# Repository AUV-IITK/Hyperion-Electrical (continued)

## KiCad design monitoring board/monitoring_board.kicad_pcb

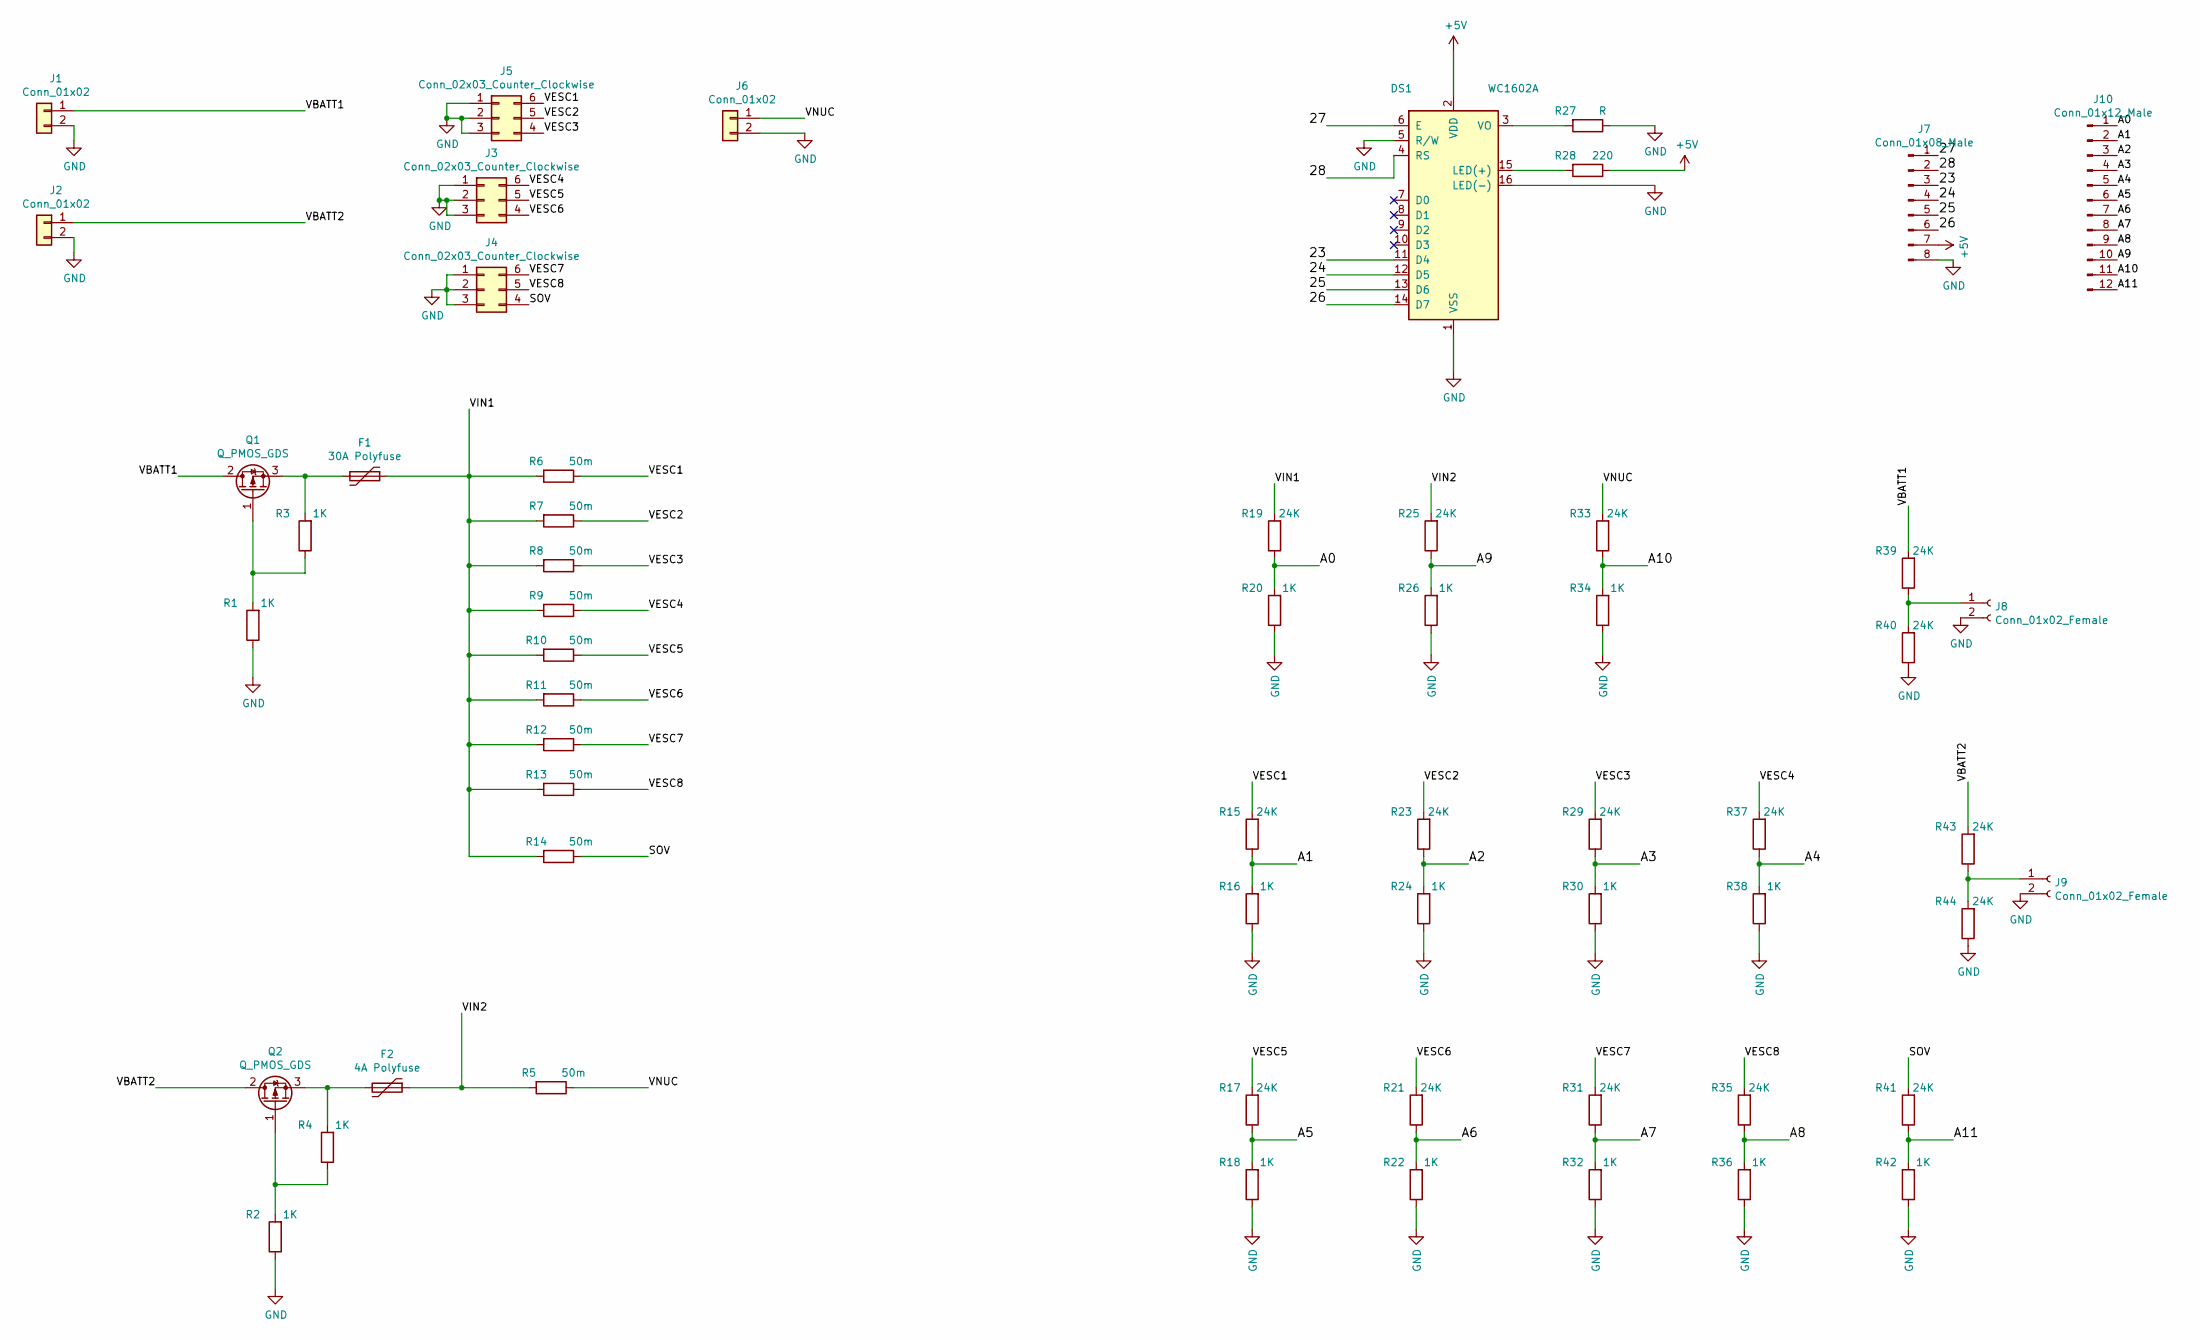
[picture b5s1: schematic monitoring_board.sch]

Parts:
DS1: WC1602A
F1: 30A Polyfuse; Fuse_TE5_Littlefuse-395Series
F2: 4A Polyfuse; Fuse_TE5_Littlefuse-395Series
J1, J2, J6: Conn_01x02; TerminalBlock_bornier-2_P5.08mm
J3, J4, J5: Conn_02x03_Counter_Clockwise; Molex_mlx32_straight_header_6.35mm
J7: Conn_01x08_Male; PinHeader_1x08_P2.54mm_Vertical
J8, J9: Conn_01x02_Female; PinSocket_1x02_P2.54mm_Vertical
J10: Conn_01x12_Male; PinHeader_1x12_P2.54mm_Vertical
Q1, Q2: Q_PMOS_GDS; TO-252-2
R1, R2, R3, R4, R16, R18, R20, R22, R24, R26, R30, R32, R34, R36, R38, R42: 1K; R_1206_3216Metric_Pad1.42x1.75mm_HandSolder
R5, R6, R7, R8, R9, R10, R11, R12, R13, R14: 50m; R_1206_3216Metric_Pad1.42x1.75mm_HandSolder
R15, R17, R19, R21, R23, R25, R29, R31, R33, R35, R37, R39, R40, R41, R43, R44: 24K; R_1206_3216Metric_Pad1.42x1.75mm_HandSolder
R27: R; R_1206_3216Metric_Pad1.42x1.75mm_HandSolder
R28: 220; R_1206_3216Metric_Pad1.42x1.75mm_HandSolder

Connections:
+5V: DS1.2 (VDD), J7.7, R28.1
/23: DS1.11 (D4), J7.3
/24: DS1.12 (D5), J7.4
/25: DS1.13 (D6), J7.5
/26: DS1.14 (D7), J7.6
/27: DS1.6 (E), J7.1
/28: DS1.4 (RS), J7.2
/A0: J10.1, R19.1, R20.2
/A1: J10.2, R15.1, R16.2
/A2: J10.3, R23.1, R24.2
/A3: J10.4, R29.1, R30.2
/A4: J10.5, R37.1, R38.2
/A5: J10.6, R17.1, R18.2
/A6: J10.7, R21.1, R22.2
/A7: J10.8, R31.1, R32.2
/A8: J10.9, R35.1, R36.2
/A9: J10.10, R25.1, R26.2
/A10: J10.11, R33.1, R34.2
/A11: J10.12, R41.1, R42.2
/SOV: J4.4, R14.1, R41.2
/VBATT1: J1.1, Q1.2 (D), R39.2
/VBATT2: J2.1, Q2.2 (D), R43.2
/VESC1: J5.6, R6.1, R15.2
/VESC2: J5.5, R7.1, R23.2
/VESC3: J5.4, R8.1, R29.2
/VESC4: J3.6, R9.1, R37.2
/VESC5: J3.5, R10.1, R17.2
/VESC6: J3.4, R11.1, R21.2
/VESC7: J4.6, R12.1, R31.2
/VESC8: J4.5, R13.1, R35.2
/VIN1: F1.1, R6.2, R7.2, R8.2, R9.2, R10.2, R11.2, R12.2, R13.2, R14.2, R19.2
/VIN2: F2.1, R5.2, R25.2
/VNUC: J6.1, R5.1, R33.2
GND: DS1.1 (VSS), DS1.5 (R/W), DS1.16 (LED(-)), J1.2, J2.2, J3.1, J3.2, J3.3, J4.1, J4.2, J4.3, J5.1, J5.2, J5.3, J6.2, J7.8, J8.2, J9.2, R1.1, R2.1, R16.1, R18.1, R20.1, R22.1, R24.1, R26.1, R27.1, R30.1, R32.1, R34.1, R36.1, R38.1, R40.1, R42.1, R44.1
unnamed: DS1.3 (VO), R27.2
unnamed: DS1.15 (LED(+)), R28.2
unnamed: F1.2, Q1.3 (S), R3.2
unnamed: F2.2, Q2.3 (S), R4.2
unnamed: J8.1, R39.1, R40.2
unnamed: J9.1, R43.1, R44.2
unnamed: Q1.1 (G), R1.2, R3.1
unnamed: Q2.1 (G), R2.2, R4.1

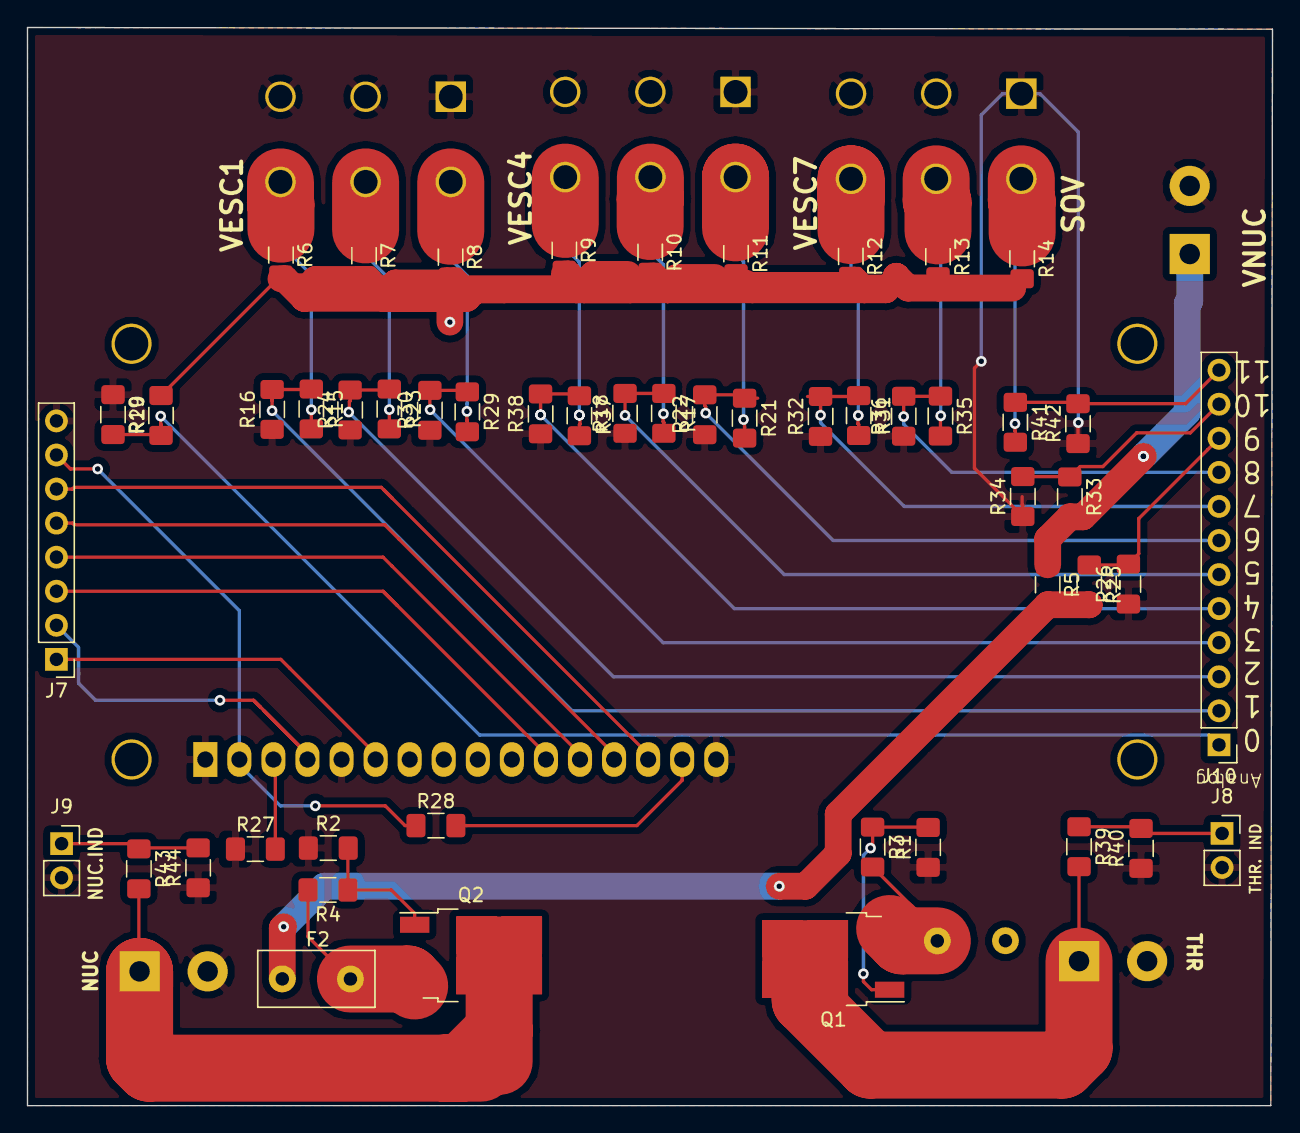
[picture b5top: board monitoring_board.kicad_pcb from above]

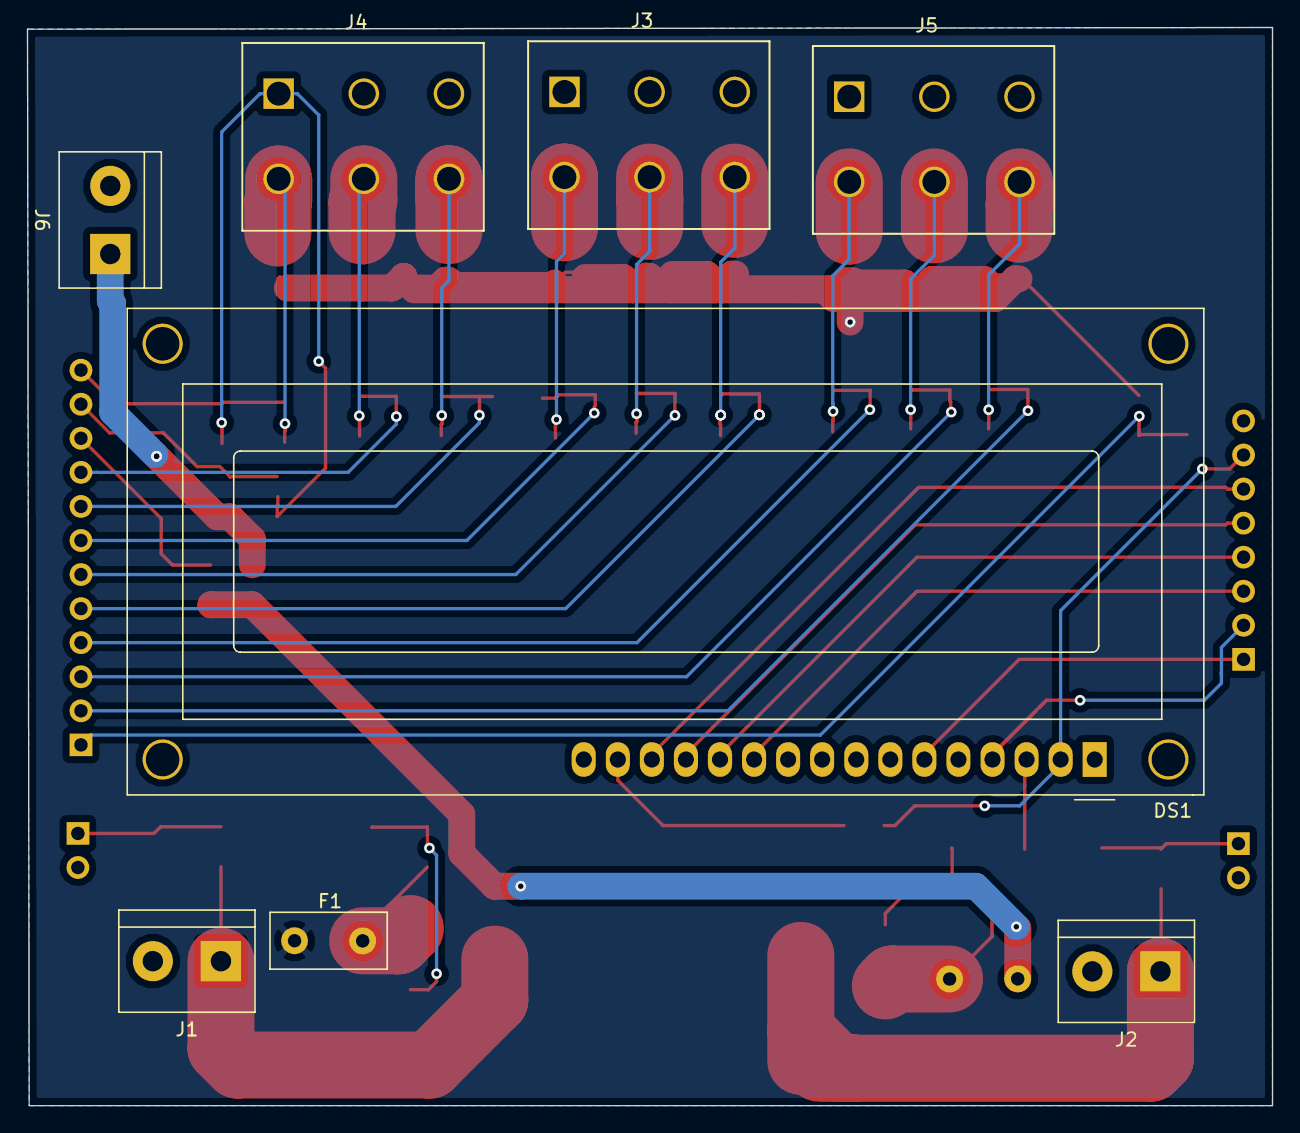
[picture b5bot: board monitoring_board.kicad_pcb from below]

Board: 2 copper layers, 92.8 x 80.4 mm, 59 parts (8 on the bottom side), 42 nets.

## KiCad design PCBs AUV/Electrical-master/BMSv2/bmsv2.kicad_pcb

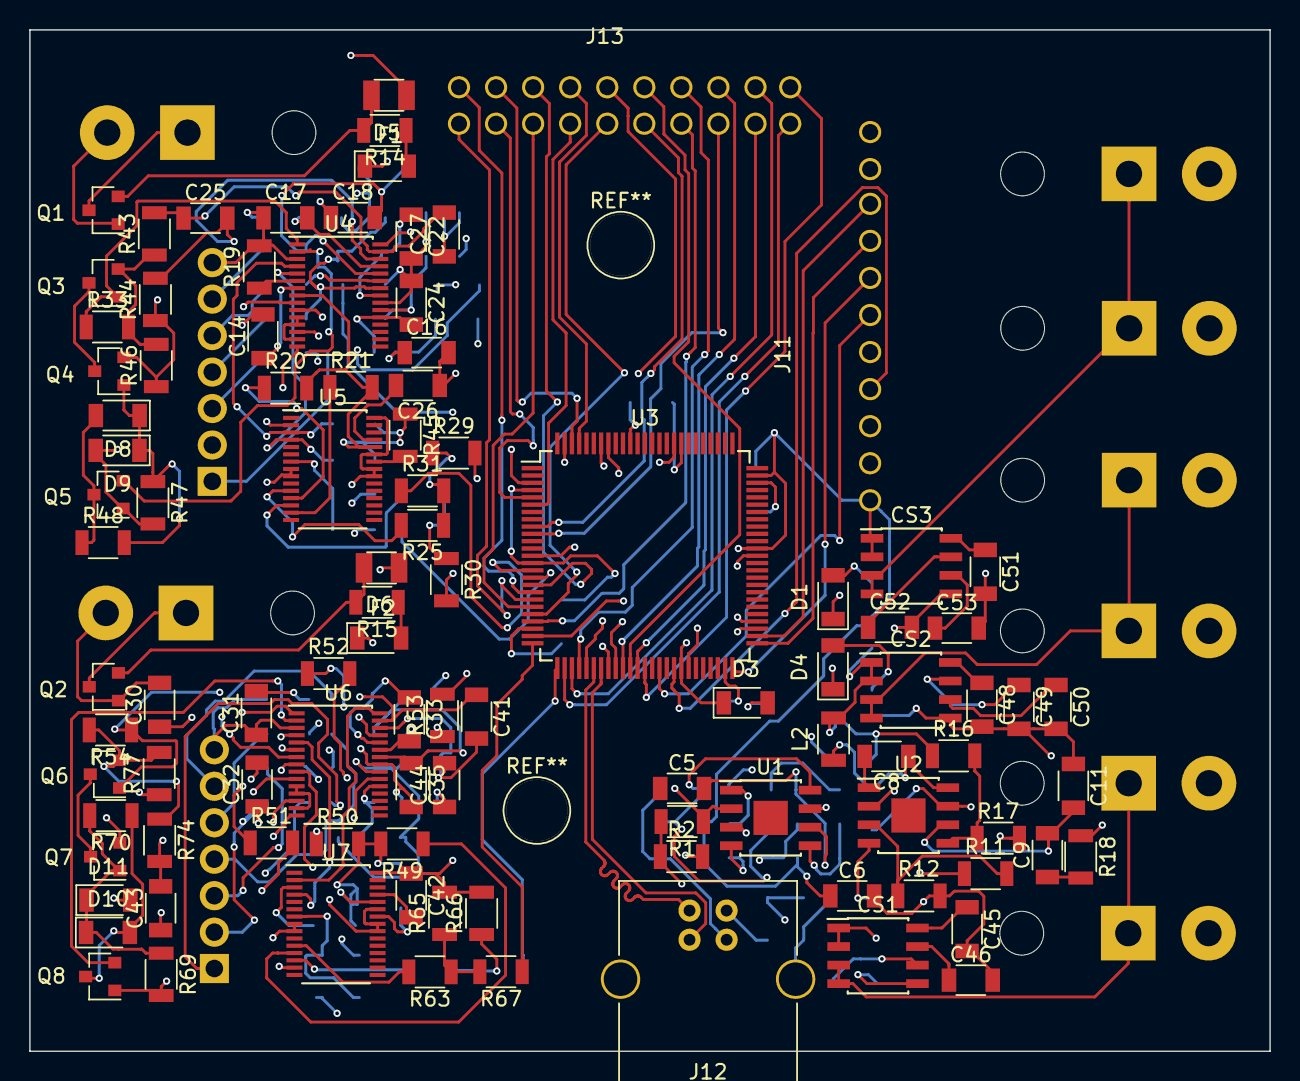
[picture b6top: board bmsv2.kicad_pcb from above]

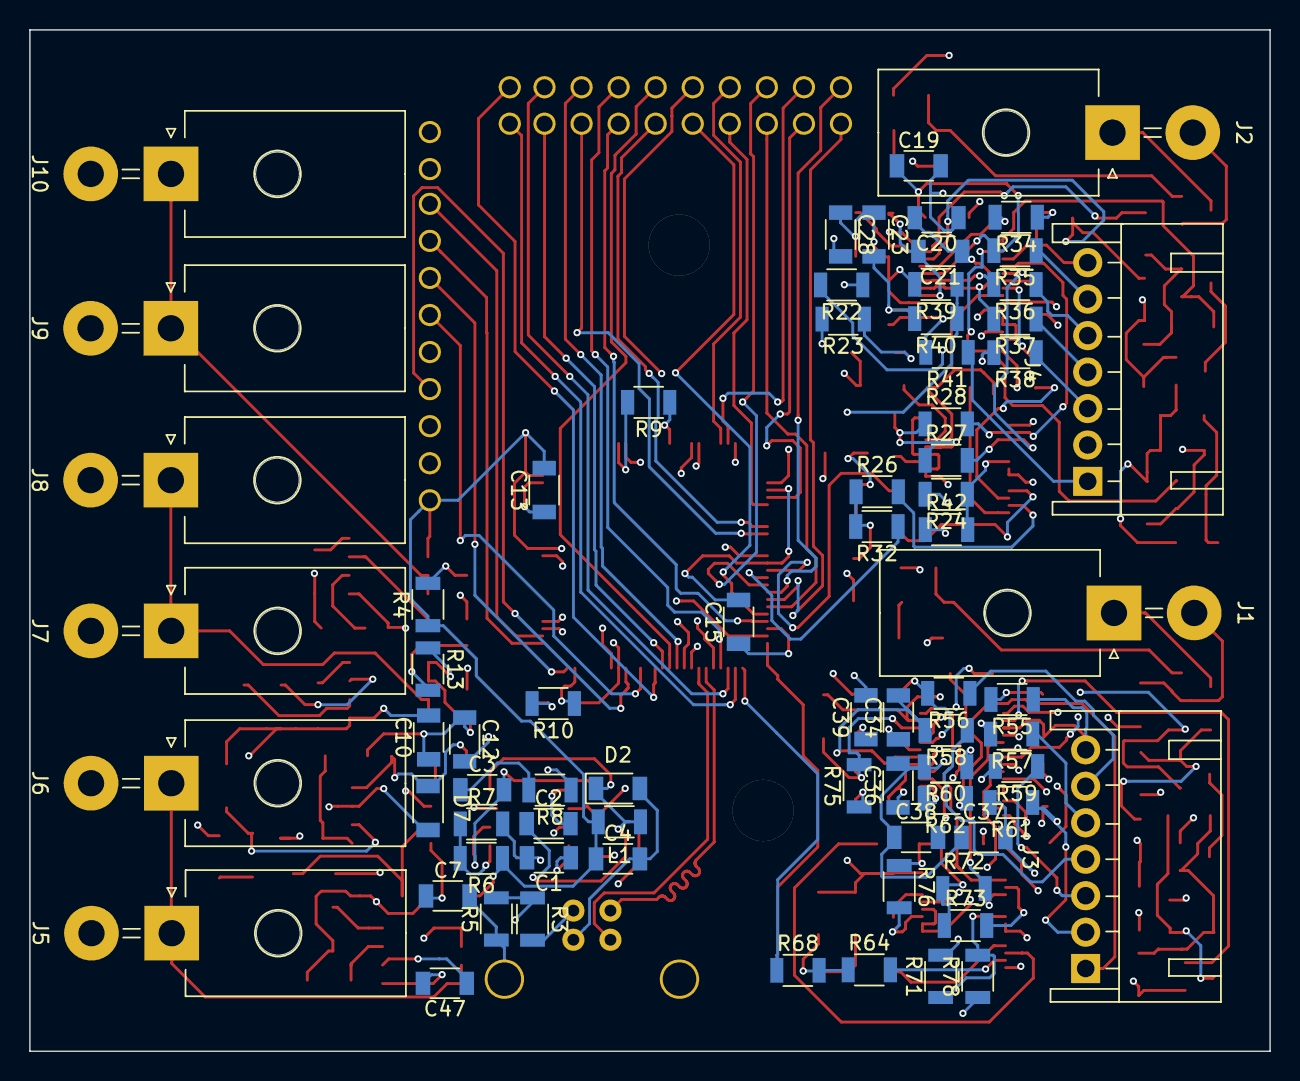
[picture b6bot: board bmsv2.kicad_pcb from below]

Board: 4 copper layers, 85.0 x 70.0 mm, 175 parts (74 on the bottom side), 156 nets.

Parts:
C1, C7: 10n; C_1206
C2, C8, C25, C26, C27, C28, C41, C42, C43, C44, C45, C48, C51: 0.1u; C_1206
C3: 3300p; C_1206
C4, C6, C10, C12: 50u; C_1206
C5: 33p; C_1206
C9: 735p; C_1206
C11: 7.35p; C_1206
C13, C15, C16, C39: 10u; C_1206
C14, C17, C18, C19, C20, C21, C22, C23, C24, C30, C31, C32, C33, C34, C35, C36, C37, C38: 1u; C_1206
C46, C47, C49, C50, C52, C53: 1n; C_1206
CS1, CS2, CS3: ACS725LLC; SOIC-8_3.9x4.9mm_Pitch1.27mm
D1, D3, D4, D5, D6: LED; D_1206
D2: 3.6V; D_1206
D7: 19V; D_1206
D8, D10: D; D_1206
D9, D11: D_Zener; D_1206
F1, F2: Fuse; Fuse_SMD1206_Reflow
J1: B1; Molex_MegaFit_2x01x5.70mm_Angled
J2: B0; Molex_MegaFit_2x01x5.70mm_Angled
J3: BC1; Wafer_Horizontal20x5.8x7RM2.5-7
J4: BC0; Wafer_Horizontal20x5.8x7RM2.5-7
J5: UnRegA; Molex_MegaFit_2x01x5.70mm_Angled
J6: UnRegB; Molex_MegaFit_2x01x5.70mm_Angled
J7: 15V0A; Molex_MegaFit_2x01x5.70mm_Angled
J8: 15V0B; Molex_MegaFit_2x01x5.70mm_Angled
J9: 3V3A; Molex_MegaFit_2x01x5.70mm_Angled
J10: 3V3B; Molex_MegaFit_2x01x5.70mm_Angled
J11: TFT_Header; Berg_11x01
J12: USB_B
J13: Atxmega_Header; Berg_10x02
L1, L2: 20u; L_1206
Q1, Q2, Q5, Q8: Q_PMOS_GSD; SOT-23
Q3, Q4, Q6, Q7: Q_NMOS_GSD; SOT-23
R1, R11: 330K; R_1206
R2, R12: 21K; R_1206
R3, R5, R13, R34, R35, R36, R37, R38, R39, R40, R41, R55, R56, R57, R58, R59, R60, R61, R62: 1K; R_1206
R4: 150; R_1206
R6: 250K; R_1206
R7, R17: 80K; R_1206
R8: 25K; R_1206
R9, R19, R22, R27, R28, R42, R51, R52, R72, R73, R78: 10K; R_1206
R10: 500; R_1206
R14, R15: 2K; R_1206
R16: 1420K; R_1206
R18: 112K; R_1206
R20, R21, R45, R49, R50, R76: 100K; R_1206
R23, R25, R26, R31, R32, R43, R44, R53, R63, R64, R67, R68, R74, R75: 100R; R_1206
R24, R71: 350K; R_1206
R29, R30, R33, R47, R48, R54, R65, R66, R69, R70: 1M; R_1206
R46, R77: R; R_1206
U1, U2: TPS54531; SOIC-8-1EP_3.9x4.9mm_Pitch1.27mm
U3: ATXMEGA128A1U-AU; TQFP-100_14x14mm_Pitch0.5mm
U4, U6: BQ76930; TSSOP-30_4.4x7.8mm_Pitch0.5mm
U5, U7: BQ78350-R1; TSSOP-30_4.4x7.8mm_Pitch0.5mm

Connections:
+3V3: C4.1, C6.1, C13.2, C15.2, CS3.1, CS3.2, J11.1, L1.2, R4.1, R6.1, R9.2, U3.4, U3.14, U3.24, U3.34, U3.44, U3.54, U3.64, U3.74, U3.83, U3.94
+15V: C10.1, C12.1, CS2.1, CS2.2, L2.2, R13.1, R16.1
+BATT: CS1.1, CS1.2, F1.1, F2.1, R1.1, R11.1, R23.2, R24.2, R53.2, R71.2, U1.2, U2.2, U4.9, U6.9
/3.3V_CS: CS3.3, CS3.4, J9.1, J10.1
/15V_CS: CS2.3, CS2.4, J7.1, J8.1
/A0: J13.4, U3.6
/A1: J13.6, U3.9
/A2: J13.8, U3.10
/ALERT0: U4.30, U5.2
/ALERT1: U6.30, U7.2
/AREF: J13.2, U3.5
/B0P0: J2.1, Q1.3
/B1P0: J1.1, Q2.3
/BAT0: R24.1, R42.2, U5.7
/BAT1: R71.1, R78.2, U7.7
/BATT_CS: CS1.3, CS1.4, J5.1, J6.1
/C01: J4.6, R35.1
/C02: J4.5, R36.1
/C03: J4.4, R37.1
/C04: J4.3, R38.1
/C05: J4.2, R39.1, R40.1
/C06: J4.1, R41.1
/C11: J3.6, R56.1
/C12: J3.5, R57.1
/C13: J3.4, R58.1
/C14: J3.3, R59.1
/C15: J3.2, R60.1, R61.1
/C16: J3.1, R62.1
/CHG0: Q5.2, U4.2
/CHG1: Q8.2, U6.2
/CSO0: C46.1, CS1.7
/CSO1: C49.1, CS2.7
/CSO2: C52.1, CS3.7
/D0: J13.10, U3.27
/D1: J13.12, U3.28
/D2: J13.14, U3.29
/D3: J13.16, U3.30
/D4: J13.18, U3.17
/D5: J13.20, U3.18
/DAC0: J13.17, U3.97
/DAC1: J13.19, U3.98
/DSG0: Q3.1, R33.1, U4.1
/DSG1: Q6.1, R54.1, U6.1
/MISO: J13.5, U3.21
/MOSI: J13.3, U3.20
/REGOUT0: R20.2, R21.2, R27.1, R28.1, R45.1, U4.8, U5.26
/REGOUT1: R49.2, R50.2, R72.1, R73.1, R76.1, U6.8, U7.26
/RSNS0: Q3.2, R33.2, R43.1, R46.2
/RSNS1: Q6.2, R54.2, R74.1, R77.2
/RX: J13.9, U3.37
/SCK: J13.7, U3.22
/SCL: J13.15, U3.36
/SCL0: R27.2, U4.5, U5.4
/SCL1: R72.2, U6.5, U7.4
/SDA: J13.13, U3.35
/SDA0: R28.2, U4.4, U5.3
/SDA1: R73.2, U6.4, U7.3
/SMBC0: R26.2, U5.13
/SMBC1: R64.2, U7.13
/SMBD0: R25.2, U5.11
/SMBD1: R63.2, U7.11
/SS: J13.1, U3.19
/TFT_CS: J11.7, U3.50
/TFT_DC: J11.9, U3.52
/TFT_MOSI: J11.6, U3.40
/TFT_RESET: J11.8, U3.51
/TFT_SCK: J11.4, U3.42
/TX: J13.11, U3.38
/USBD+: J12.3, U3.32
/USBD-: J12.2, U3.31
/USB_VCC: R3.1, R5.2, U3.99
/VC00: C17.2, R34.2, U4.27
/VC01: C18.2, C19.1, R35.2, U4.26
/VC02: C19.2, C20.1, R36.2, U4.25
/VC03: C20.2, C21.1, R37.2, U4.24
/VC04: C21.2, C22.1, R38.2, U4.23
/VC05: C22.2, C23.1, C24.1, R39.2, U4.22
/VC05B: C23.2, R40.2, U4.21
/VC06: C24.2, R41.2, U4.20
/VC10: C31.2, R55.2, U6.27
/VC11: C32.2, C33.1, R56.2, U6.26
/VC12: C33.2, C34.1, R57.2, U6.25
/VC13: C34.2, C35.1, R58.2, U6.24
/VC14: C35.2, C36.1, R59.2, U6.23
/VC15: C36.2, C37.1, C38.1, R60.2, U6.22
/VC15B: C37.2, R61.2, U6.21
/VC16: C38.2, R62.2, U6.20
/uSCL0: R32.1, U3.16
/uSCL1: R68.1, U3.26
/uSDA0: R31.1, U3.15
/uSDA1: R67.1, U3.25
GND: C1.2, C4.2, C5.1, C6.2, C7.2, C10.2, C11.1, C12.2, C13.1, C14.2, C15.1, C16.2, C17.1, C18.1, C26.1, C27.1, C28.1, C30.2, C31.1, C32.1, C39.2, C42.1, C43.1, C44.1, C45.2, C46.2, C47.2, C48.2, C49.2, C50.2, C51.2, C52.2, C53.2, CS1.5, CS2.5, CS3.5, D1.1, D2.2, D3.1, D4.1, D5.1, D6.1, D7.2, D9.2, D11.2, J1.2, J2.2, J3.7, J4.7, J5.2, J6.2, J7.2, J8.2, J9.2, J10.2, J11.3, J12.4, J12.5, Q1.1, Q2.1, Q4.2, Q5.1, Q7.2, Q8.1, R2.2, R5.1, R7.2, R8.1, R12.2, R17.2, R18.1, R19.2, R29.2, R30.2, R34.1, R42.1, R44.1, R46.1, R47.2, R51.2, R55.1, R65.2, R66.2, R69.2, R75.1, R77.1, R78.1, U1.7, U2.7, U3.3, U3.13, U3.23, U3.33, U3.43, U3.53, U3.63, U3.73, U3.84, U3.93, U4.3, U5.8, U5.9, U5.22, U5.23, U5.25, U5.30, U6.3, U7.8, U7.9, U7.22, U7.23, U7.25, U7.30
unnamed: C1.1, U1.4
unnamed: C2.1, D2.1, L1.1, U1.8
unnamed: C2.2, U1.1
unnamed: C3.1, R8.2
unnamed: C3.2, C5.2, U1.6
unnamed: C7.1, U2.4
unnamed: C8.1, D7.1, L2.1, U2.8
unnamed: C8.2, U2.1
unnamed: C9.1, R18.2
unnamed: C9.2, C11.2, U2.6
unnamed: C14.1, U4.7
unnamed: C16.1, R23.1, U4.15
unnamed: C25.1, C27.2, R43.2, U4.29
unnamed: C25.2, C28.2, R44.2, U4.28
unnamed: C26.2, U5.27
unnamed: C30.1, U6.7
unnamed: C39.1, R53.1, U6.15
unnamed: C41.1, C43.2, R74.2, U6.29
unnamed: C41.2, C44.2, R75.2, U6.28
unnamed: C42.2, U7.27
unnamed: C45.1, CS1.8
unnamed: C47.1, CS1.6
unnamed: C48.1, CS2.8
unnamed: C50.1, CS2.6
unnamed: C51.1, CS3.8
unnamed: C53.1, CS3.6
unnamed: D1.2, R4.2
unnamed: D3.2, R10.2
unnamed: D4.2, R13.2
unnamed: D5.2, R14.1
unnamed: D6.2, R15.1
unnamed: D8.1, D9.1, Q4.1, R47.1, R48.2
unnamed: D8.2, Q5.3, R48.1
unnamed: D10.1, D11.1, Q7.1, R69.1, R70.2
unnamed: D10.2, Q8.3, R70.1
unnamed: F1.2, Q1.2, R14.2
unnamed: F2.2, Q2.2, R15.2
unnamed: J12.1, R3.2
unnamed: Q3.3, Q4.3
unnamed: Q6.3, Q7.3
unnamed: R1.2, R2.1, U1.3
unnamed: R6.2, R7.1, U1.5
unnamed: R9.1, U3.90
unnamed: R10.1, U3.49
unnamed: R11.2, R12.1, U2.3
unnamed: R16.2, R17.1, U2.5
unnamed: R19.1, U4.6
unnamed: R20.1, U5.12
unnamed: R21.1, U5.14
unnamed: R22.1, U4.10
unnamed: R22.2, U4.13
unnamed: R25.1, R29.1, R31.2
unnamed: R26.1, R30.1, R32.2
unnamed: R45.2, U5.24
unnamed: R49.1, U7.12
unnamed: R50.1, U7.14
unnamed: R51.1, U6.6
unnamed: R52.1, U6.10
unnamed: R52.2, U6.13
unnamed: R63.1, R65.1, R67.2
unnamed: R64.1, R66.1, R68.2
unnamed: R76.2, U7.24
unnamed: U4.11, U4.12, U4.14
unnamed: U6.11, U6.12, U6.14
